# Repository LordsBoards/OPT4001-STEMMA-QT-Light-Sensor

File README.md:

# OPT4001 STEMMA QT Ambient Light Sensor Board 🌞

A custom STEMMA QT compatible board featuring the OPT4001 high-precision ambient light sensor in SOT-5X3 package.

Features

- 📏 STEMMA QT / Qwiic compatible
- 🌈 OPT4001 sensor with human eye-like response
- 🔢 28-bit effective dynamic range
- 🔌 3.3V operation, 5V tolerant I/O
- 🧱 Designed in KiCAD 8

Specs

- Sensor: TI OPT4001 (SOT-5X3)
- Interface: I2C
- Voltage: 3.3V (5V tolerant SDA/SCL/INT)
- Connectors: 2x STEMMA QT / Qwiic

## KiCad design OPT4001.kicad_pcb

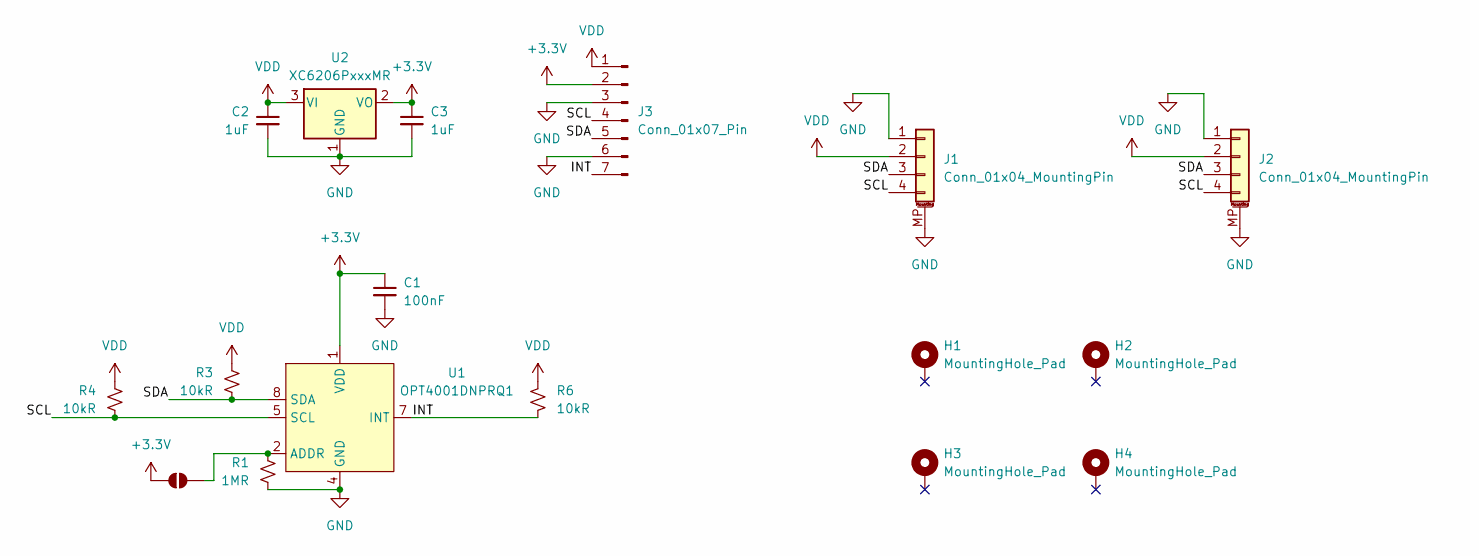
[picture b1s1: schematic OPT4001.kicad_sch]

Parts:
C1: 100nF; C_0402_1005Metric; LCSC C1525
C2, C3: 1uF; C_0402_1005Metric; LCSC C52923
H1, H2, H3, H4: MountingHole_Pad; MountingHole_2.5mm_Pad
J1, J2: Conn_01x04_MountingPin; JST_SH_SM04B-SRSS-TB_1x04-1MP_P1.00mm_Horizontal; LCSC C371571
J3: Conn_01x07_Pin; PinHeader_1x07_P2.54mm_Vertical
JP1: SolderJumper_2_Open; SolderJumper-2_P1.3mm_Open_RoundedPad1.0x1.5mm
R1: 1MR; R_0402_1005Metric; LCSC C26083
R3, R4, R6: 10kR; R_0402_1005Metric; LCSC C25744
U1: OPT4001DNPRQ1; SOT-5X3; LCSC C17612395
U2: XC6206PxxxMR; SOT-23-3; LCSC C5446

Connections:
+3.3V: C1.1, C3.1, J3.2, JP1.1 (A), U1.1 (VDD), U2.2 (VO)
/INT: J3.7, R6.2, U1.7 (INT)
/SCL: J1.4, J2.4, J3.4, R4.2, U1.5 (SCL)
/SDA: J1.3, J2.3, J3.5, R3.2, U1.8 (SDA)
GND: C1.2, C2.2, C3.2, J1.1, J1.MP (MountPin), J2.1, J2.MP (MountPin), J3.3, J3.6, R1.2, U1.4 (GND), U2.1 (GND)
unnamed: JP1.2 (B), R1.1, U1.2 (ADDR)
VDD: C2.1, J1.2, J2.2, J3.1, R3.1, R4.1, R6.1, U2.3 (VI)

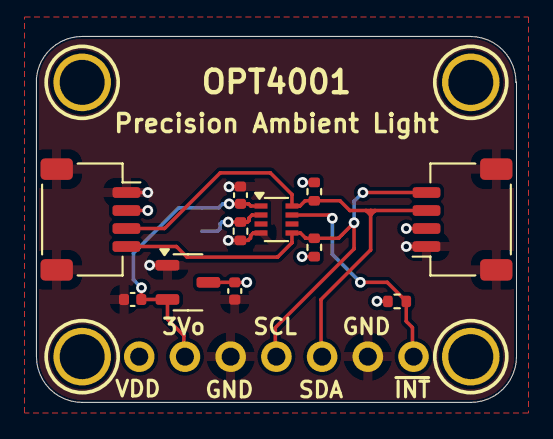
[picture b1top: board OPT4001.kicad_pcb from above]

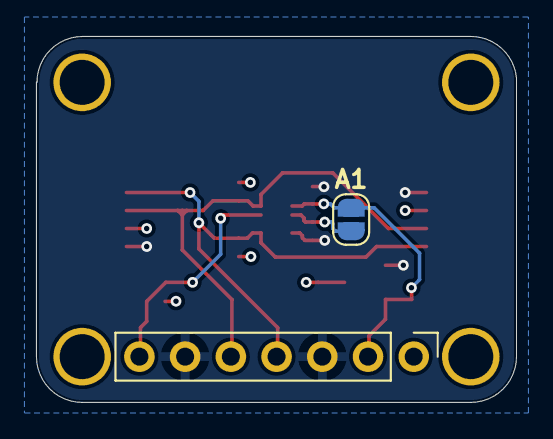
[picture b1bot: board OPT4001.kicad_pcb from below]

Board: 4 copper layers, 26.7 x 20.3 mm, 17 parts (2 on the bottom side), 7 nets.

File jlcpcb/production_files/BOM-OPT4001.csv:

Comment,Designator,Footprint,LCSC
100nF,C1,C_0402_1005Metric,C1525
OPT4001DNPRQ1,U1,SOT-5X3,C17612395
10kR,"R3,R4,R6",R_0402_1005Metric,C25744
1MR,R1,R_0402_1005Metric,C26083
Conn_01x04_MountingPin,"J1,J2",JST_SH_SM04B-SRSS-TB_1x04-1MP_P1.00mm_Horizontal,C371571
1uF,"C2,C3",C_0402_1005Metric,C52923
XC6206PxxxMR,U2,SOT-23-3,C5446
Conn_01x07_Pin,J3,PinHeader_1x07_P2.54mm_Vertical,

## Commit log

2024-08-02 Initial commit.
2024-08-02 added image
